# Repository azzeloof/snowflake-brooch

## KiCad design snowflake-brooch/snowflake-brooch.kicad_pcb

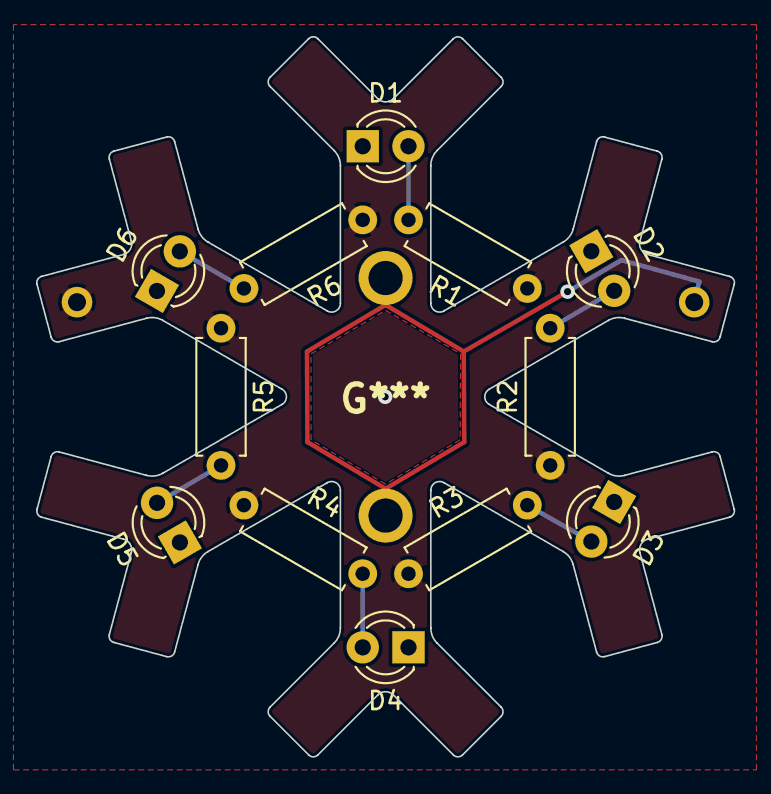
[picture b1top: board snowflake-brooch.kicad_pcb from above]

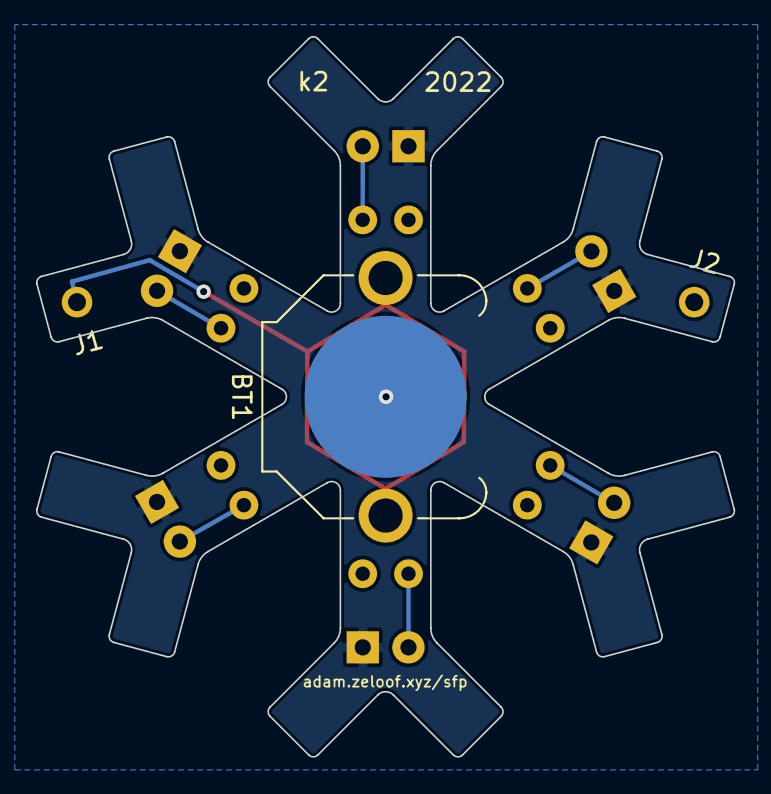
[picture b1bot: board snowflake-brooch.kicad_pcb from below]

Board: 2 copper layers, 38.8 x 40.0 mm, 15 parts (3 on the bottom side), 9 nets.

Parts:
BT1: Battery; BatteryHolder_Keystone_3001_1x12mm
D1, D2, D3, D4, D5, D6: LED; LED_D3.0mm
J1, J2: Pin; PinHeader_1x01_P2.54mm_Vertical
R1, R2, R3, R4, R5, R6: R_US; R_Axial_DIN0207_L6.3mm_D2.5mm_P7.62mm_Horizontal

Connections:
GND: BT1.2 (-), D1.1 (K), D2.1 (K), D3.1 (K), D4.1 (K), D5.1 (K), D6.1 (K)
unnamed: BT1.1 (+), J1.1
unnamed: D1.2 (A), R1.2
unnamed: D2.2 (A), R2.2
unnamed: D3.2 (A), R3.2
unnamed: D4.2 (A), R4.2
unnamed: D5.2 (A), R5.2
unnamed: D6.2 (A), R6.2
VCC: J2.1, R1.1, R2.1, R3.1, R4.1, R5.1, R6.1
